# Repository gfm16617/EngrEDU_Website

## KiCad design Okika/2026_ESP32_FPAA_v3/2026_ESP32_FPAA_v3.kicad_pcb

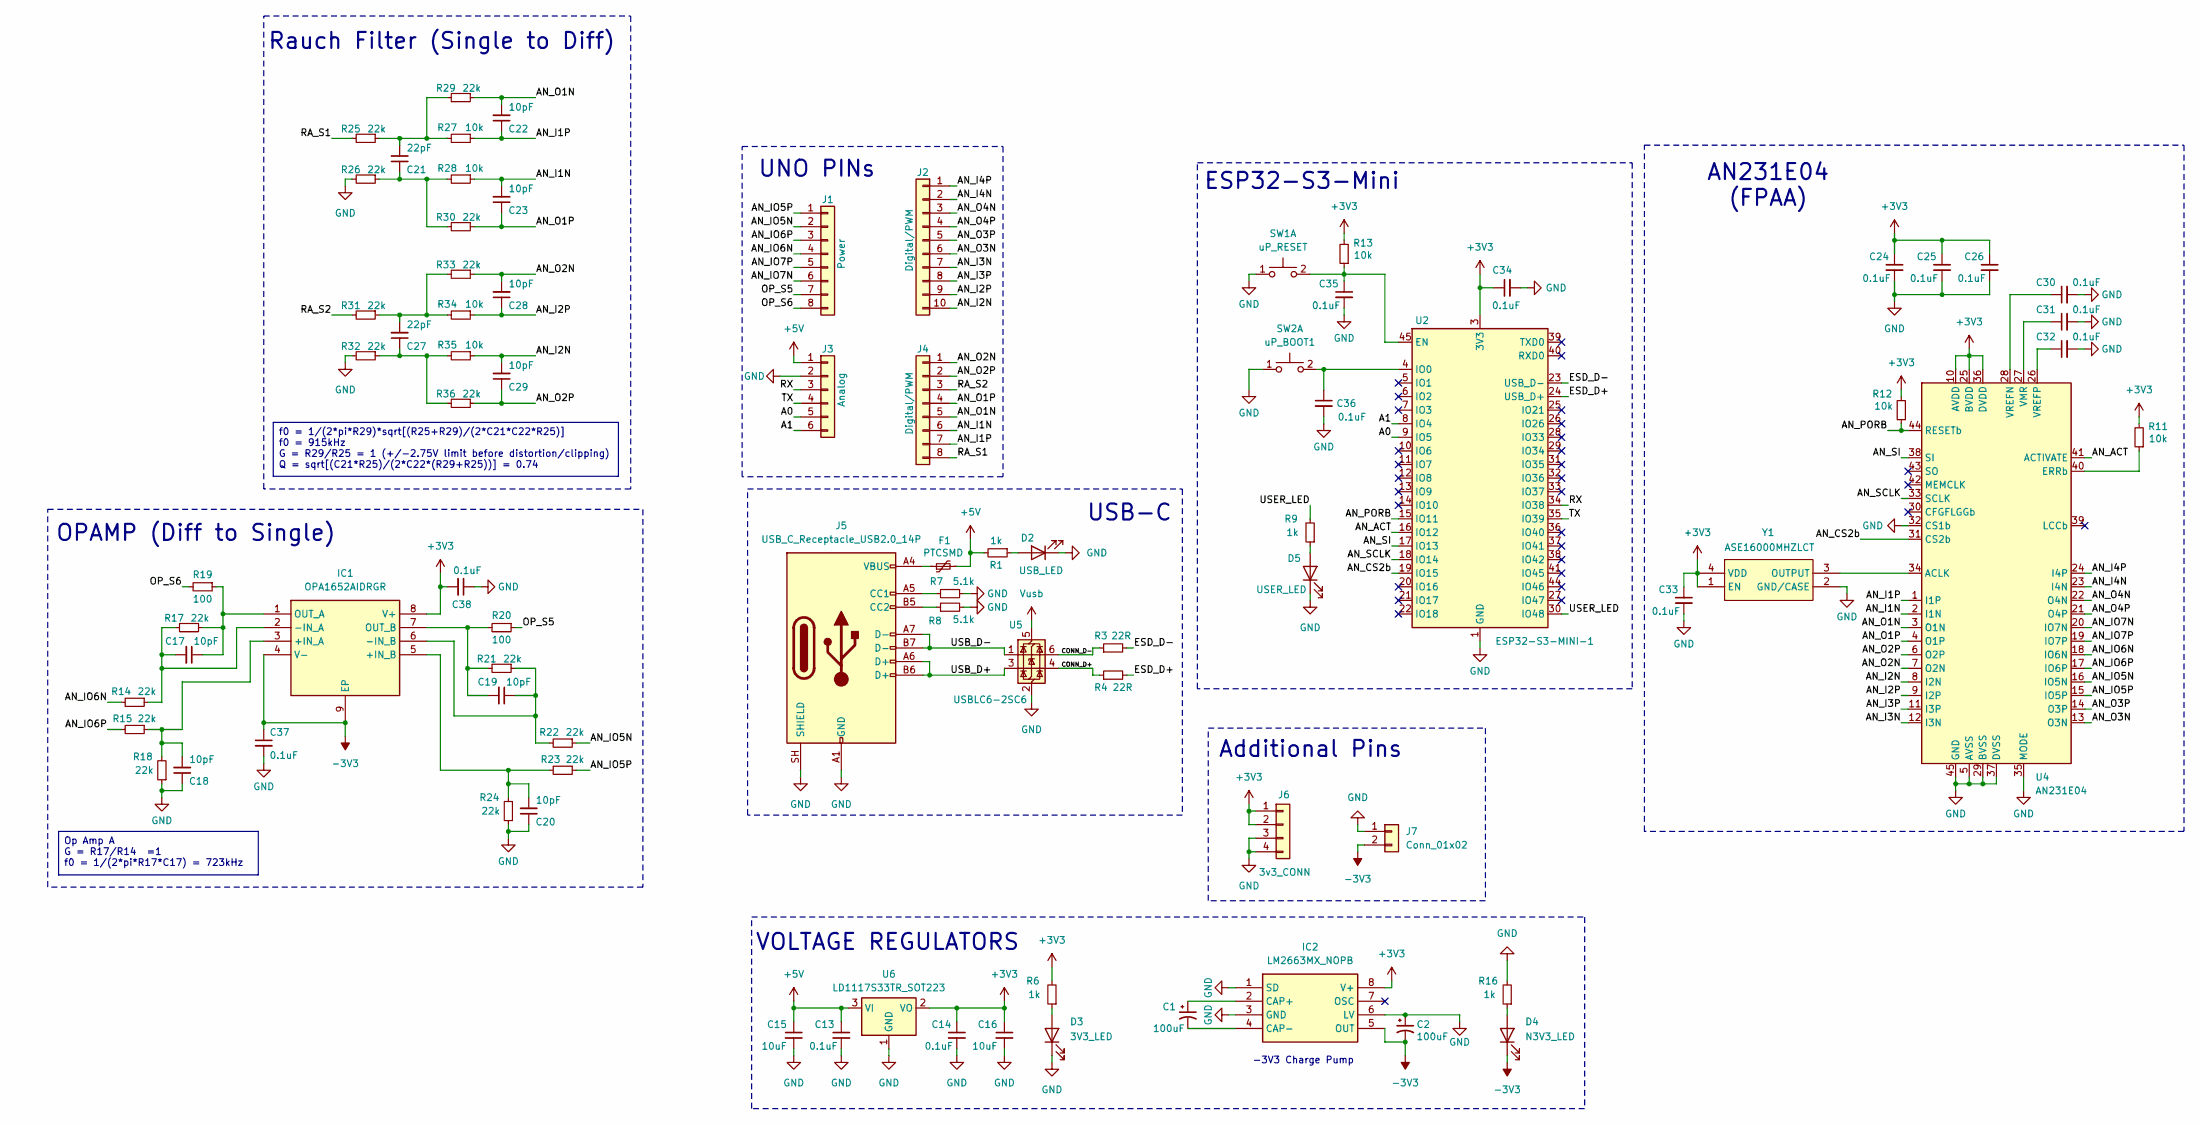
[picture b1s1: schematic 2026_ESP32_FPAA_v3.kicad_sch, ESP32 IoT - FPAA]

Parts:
C1, C2: 100uF; CAPPM7343X310N; Mfr # 593D107X9010D2TE3
C13, C14, C34, C35, C36, C37, C38: 0.1uF; C_0805_2012Metric_Pad1.18x1.45mm_HandSolder; Mfr # C0805C104K4JACAUTO
C15, C16: 10uF; C_0805_2012Metric_Pad1.18x1.45mm_HandSolder; Mfr # C0805C106K4PACTU
C17, C18, C19, C20, C22, C23, C28, C29: 10pF; C_0603_1608Metric_Pad1.08x0.95mm_HandSolder; Mfr # 08052U100JAT2A
C21, C27: 22pF; C_0603_1608Metric_Pad1.08x0.95mm_HandSolder; Mfr # C0603C220G3HACTU
C24, C25, C26, C30, C31, C32, C33: 0.1uF; C_0603_1608Metric_Pad1.08x0.95mm_HandSolder; Mfr # CC0603JRX7R9BB104
D2: USB_LED; LED_0805_2012Metric_Pad1.15x1.40mm_HandSolder; Mfr # 150080BS75000
D3: 3V3_LED; LED_0805_2012Metric_Pad1.15x1.40mm_HandSolder; Mfr # 150080BS75000
D4: N3V3_LED; LED_0805_2012Metric_Pad1.15x1.40mm_HandSolder; Mfr # 150080BS75000
D5: USER_LED; LED_0805_2012Metric_Pad1.15x1.40mm_HandSolder; Mfr # 150080BS75000
F1: PTCSMD; Fuse_1812_4532Metric; Mfr # MF-MSMF050-2
IC1: OPA1652AIDRGR; SON50P300X300X80-9N-D; Manufacturer_Part_Number OPA1652AIDRGR; Mouser Part Number 595-OPA1652AIDRGR
IC2: LM2663MX_NOPB; SOIC127P600X175-8N; Manufacturer_Part_Number LM2663MX/NOPB; Mouser Part Number 926-LM2663MX/NOPB
J1: Power; PinSocket_1x08_P2.54mm_Vertical
J2: Digital/PWM; PinSocket_1x10_P2.54mm_Vertical
J3: Analog; PinSocket_1x06_P2.54mm_Vertical
J4: Digital/PWM; PinSocket_1x08_P2.54mm_Vertical
J5: USB_C_Receptacle_USB2.0_14P; USB_C_Receptacle_HCTL_HC-TYPE-C-16P-01A; Mfg Part# UJ20-C-H-C-4-SMT-TR
J6: 3v3_CONN; PinHeader_1x04_P2.54mm_Vertical
J7: Conn_01x02; PinHeader_1x02_P2.54mm_Vertical
R1, R6, R9, R16: 1k; R_0805_2012Metric_Pad1.20x1.40mm_HandSolder; Mfr # TNPW08051K00FEEA
R3, R4: 22R; R_0805_2012Metric_Pad1.20x1.40mm_HandSolder; Mfr # RCA080522R0FKEA
R7: 5.1k; R_0805_2012Metric_Pad1.20x1.40mm_HandSolder; Mfg Part# AC0805FR-075K1L
R8: 5.1k; R_0805_2012Metric_Pad1.20x1.40mm_HandSolder; Mfg Part# CRCW06035K10FKEC
R11, R12, R27, R28, R34, R35: 10k; R_0603_1608Metric_Pad0.98x0.95mm_HandSolder; Mfr # AC0805DR-0710KL
R13: 10k; R_0805_2012Metric_Pad1.20x1.40mm_HandSolder; Mfr # AC0805DR-0710KL
R14, R15, R17, R18, R21, R22, R23, R24, R25, R26, R29, R30, R31, R32, R33, R36: 22k; R_0603_1608Metric_Pad0.98x0.95mm_HandSolder; Mfr # RT0805DRD0722KL
R19, R20: 100; R_0603_1608Metric_Pad0.98x0.95mm_HandSolder; Mfr # RT0805FRE10100RL
SW1: uP_RESET; SW_SWT7015-006010SSA_REVA; Mfr # SWT7015-006010SSA
SW2: uP_BOOT1; SW_SWT7015-006010SSA_REVA; Mfr # SWT7015-006010SSA
U2: ESP32-S3-MINI-1; ESP32-S2-MINI-1; Mfr # ESP32-S3-MINI-1-N8
U4: AN231E04; QFN-44-1EP_7x7mm_P0.5mm_EP5.15x5.15mm; Part # AN231E04
U5: USBLC6-2SC6; SOT-23-6; Mfr # USBLC6-2SC6
U6: LD1117S33TR_SOT223; SOT-223-3_TabPin2; Mfr # LD1117S33TR
Y1: ASE16000MHZLCT; ASE24576MHZLCT; Manufacturer_Part_Number ASE16000MHZLCT

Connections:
+3V3: C14.1, C16.1, C24.1, C25.1, C26.1, C33.1, C34.1, C38.2, IC1.8 (V+), IC2.8 (V+), J6.1, J6.2, R6.2, R11.2, R12.2, R13.2, U2.3 (3V3), U4.10 (AVDD), U4.25 (BVDD), U4.36 (DVDD), U6.2 (VO), Y1.1 (EN), Y1.4 (VDD)
+5V: C13.1, C15.1, F1.2, J3.1, R1.2, U6.3 (VI)
-3V3: C2.2, C37.1, D4.1 (K), IC1.4 (V-), IC1.9 (EP), IC2.5 (OUT), J7.2
/A0: J3.5, U2.9 (IO5)
/A1: J3.6, U2.8 (IO4)
/AN_ACT: U2.16 (IO12), U4.41 (ACTIVATE)
/AN_CS2b: U2.19 (IO15), U4.31 (CS2b)
/AN_I1N: C23.2, J4.6, R28.1, U4.2 (I1N)
/AN_I1P: C22.1, J4.7, R27.1, U4.1 (I1P)
/AN_I2N: C29.2, J2.10, R35.1, U4.8 (I2N)
/AN_I2P: C28.1, J2.9, R34.1, U4.9 (I2P)
/AN_I3N: J2.7, U4.12 (I3N)
/AN_I3P: J2.8, U4.11 (I3P)
/AN_I4N: J2.2, U4.23 (I4N)
/AN_I4P: J2.1, U4.24 (I4P)
/AN_IO5N: J1.2, R22.1, U4.16 (IO5N)
/AN_IO5P: J1.1, R23.1, U4.15 (IO5P)
/AN_IO6N: J1.4, R14.2, U4.18 (IO6N)
/AN_IO6P: J1.3, R15.2, U4.17 (IO6P)
/AN_IO7N: J1.6, U4.20 (IO7N)
/AN_IO7P: J1.5, U4.19 (IO7P)
/AN_O1N: C22.2, J4.5, R29.1, U4.3 (O1N)
/AN_O1P: C23.1, J4.4, R30.1, U4.4 (O1P)
/AN_O2N: C28.2, J4.1, R33.1, U4.7 (O2N)
/AN_O2P: C29.1, J4.2, R36.1, U4.6 (O2P)
/AN_O3N: J2.6, U4.13 (O3N)
/AN_O3P: J2.5, U4.14 (O3P)
/AN_O4N: J2.3, U4.22 (O4N)
/AN_O4P: J2.4, U4.21 (O4P)
/AN_PORB: R12.1, U2.15 (IO11), U4.44 (RESETb)
/AN_SCLK: U2.18 (IO14), U4.33 (SCLK)
/AN_SI: U2.17 (IO13), U4.38 (SI)
/CONN_D+: R4.1, U5.4 (I/O2)
/CONN_D-: R3.1, U5.6 (I/O1)
/ESD_D+: R4.2, U2.24 (USB_D+)
/ESD_D-: R3.2, U2.23 (USB_D-)
/OP_S5: J1.7, R20.1
/OP_S6: J1.8, R19.2
/RA_S1: J4.8, R25.2
/RA_S2: J4.3, R31.2
/RX: J3.3, U2.34 (IO38)
/TX: J3.4, U2.35 (IO39)
/USB_D+: J5.A6 (D+), J5.B6 (D+), U5.3 (I/O2)
/USB_D-: J5.A7 (D-), J5.B7 (D-), U5.1 (I/O1)
/USER_LED: R9.2, U2.30 (IO48)
GND: C2.1, C13.2, C14.2, C15.2, C16.2, C18.1, C20.1, C24.2, C25.2, C26.2, C30.2, C31.2, C32.2, C33.2, C34.2, C35.2, C36.2, C37.2, C38.1, D2.1 (K), D3.1 (K), D5.1 (K), IC2.1 (SD), IC2.3 (GND), IC2.6 (LV), J3.2, J5.A1 (GND), J5.A12 (GND), J5.B1 (GND), J5.B12 (GND), J5.SH (SHIELD), J6.3, J6.4, J7.1, R7.1, R8.2, R16.2, R18.1, R24.1, R26.2, R32.2, SW1.1 (C), SW2.1 (C), U2.1 (GND), U2.2 (GND), U2.42 (GND), U2.43 (GND), U2.46 (GND), U2.47 (GND), U2.48 (GND), U2.49 (GND), U2.50 (GND), U2.51 (GND), U2.52 (GND), U2.53 (GND), U2.54 (GND), U2.55 (GND), U2.56 (GND), U2.57 (GND), U2.58 (GND), U2.59 (GND), U2.60 (GND), U2.61 (GND), U2.62 (GND), U2.63 (GND), U2.64 (GND), U2.65 (GND), U4.5 (AVSS), U4.29 (BVSS), U4.32 (CS1b), U4.35 (MODE), U4.37 (DVSS), U4.45 (GND), U5.2 (GND), U6.1 (GND), Y1.2 (GND/CASE)
unnamed: C21.1, R26.1, R28.2, R30.2
unnamed: C21.2, R25.1, R27.2, R29.2
unnamed: C27.1, R32.1, R35.2, R36.2
unnamed: C27.2, R31.1, R33.2, R34.2
unnamed: D2.2 (A), R1.1
unnamed: D3.2 (A), R6.1
unnamed: D4.2 (A), R16.1
unnamed: D5.2 (A), R9.1
unnamed: F1.1, J5.A4 (VBUS), J5.A9 (VBUS), J5.B4 (VBUS), J5.B9 (VBUS)
unnamed: C18.2, IC1.3 (+IN_A), R15.1, R18.2
unnamed: C20.2, IC1.5 (+IN_B), R23.2, R24.2
unnamed: C17.2, IC1.2 (-IN_A), R14.1, R17.2
unnamed: C19.1, IC1.6 (-IN_B), R21.1, R22.2
unnamed: C17.1, IC1.1 (OUT_A), R17.1, R19.1
unnamed: C19.2, IC1.7 (OUT_B), R20.2, R21.2
unnamed: C1.1, IC2.2 (CAP+)
unnamed: C1.2, IC2.4 (CAP-)
unnamed: J5.A5 (CC1), R7.2
unnamed: J5.B5 (CC2), R8.1
unnamed: C35.1, R13.1, SW1.2 (D), U2.45 (EN)
unnamed: C36.1, SW2.2 (D), U2.4 (IO0)
unnamed: U4.34 (ACLK), Y1.3 (OUTPUT)
unnamed: R11.1, U4.40 (ERRb)
unnamed: C31.1, U4.27 (VMR)
unnamed: C30.1, U4.28 (VREFN)
unnamed: C32.1, U4.26 (VREFP)
Vusb: U5.5 (VBUS)

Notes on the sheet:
USB-C
ESP32-S3-Mini
Additional Pins
OPAMP (Diff to Single)
-3V3 Charge Pump
VOLTAGE REGULATORS
Rauch Filter (Single to Diff)
AN231E04 (FPAA)
UNO PINs
f0 = 1/(2*pi*R29)*sqrt[(R25+R29)/(2*C21*C22*R25)] f0 = 915kHz G = R29/R25 = 1 (+/-2.75V limit before distortion/clipping) Q = sqrt[(C21*R25)/(2*C22*(R29+R25))] = 0.74
Op Amp A G = R17/R14 =1 f0 = 1/(2*pi*R17*C17) = 723kHz

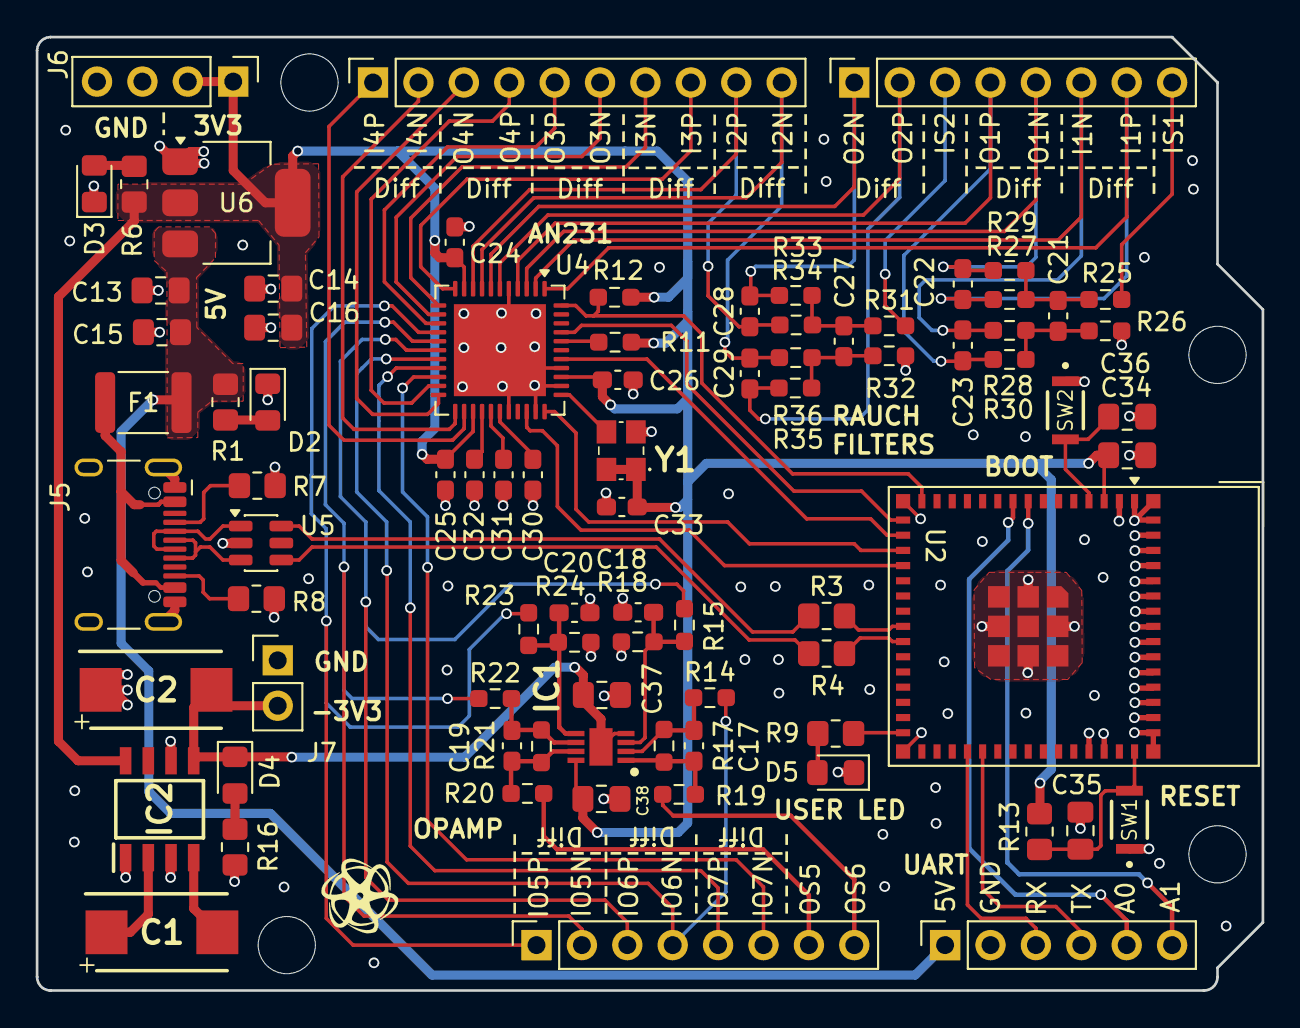
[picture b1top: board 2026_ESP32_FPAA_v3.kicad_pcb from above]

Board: 4 copper layers, 68.6 x 53.3 mm, 86 parts (0 on the bottom side), 72 nets.

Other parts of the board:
MH1, MH2, MH3, MH4: MountingHole_3.2mm

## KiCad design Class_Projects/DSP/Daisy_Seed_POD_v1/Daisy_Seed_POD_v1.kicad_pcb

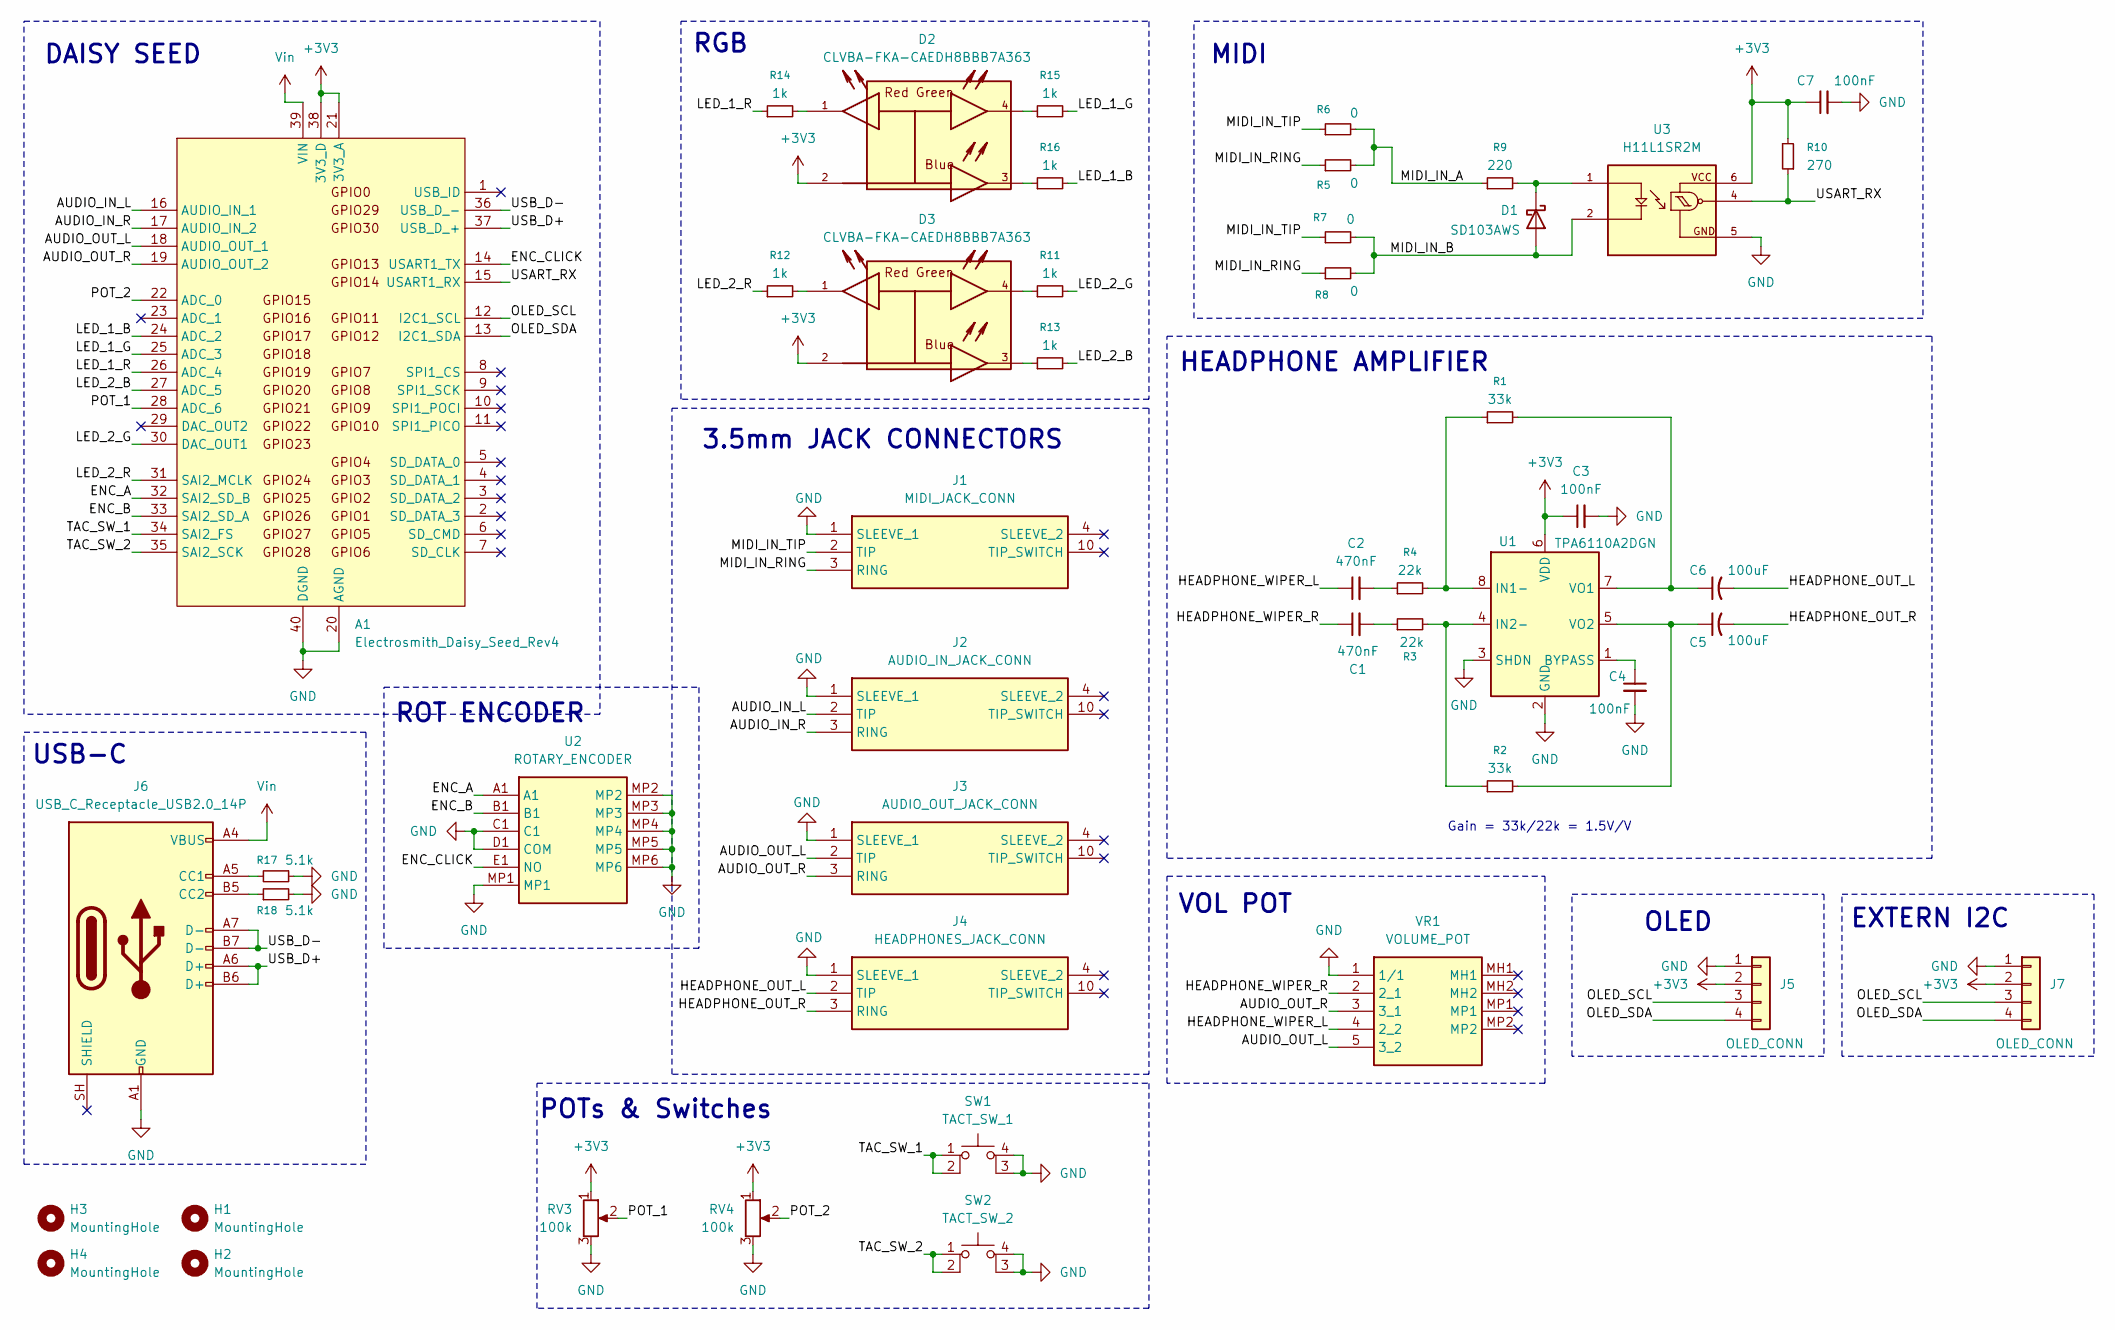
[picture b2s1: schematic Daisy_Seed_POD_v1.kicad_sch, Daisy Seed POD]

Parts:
A1: Electrosmith_Daisy_Seed_Rev4; Electrosmith_Daisy_Seed
C1, C2: 470nF; C_0805_2012Metric; Mfr # GCJ21BL8EH474KA07L
C3, C4, C7: 100nF; C_0805_2012Metric; Mfr # 0805YC104M4T2A
C5, C6: 100uF; CAP_EEE1AA101SP; Mfr # EEE-1AA101SP
D1: SD103AWS; SOD2513X120N; Mfr # SD103AWS-7-F
D2, D3: CLVBA-FKA-CAEDH8BBB7A363; SOL150P350X210-4N; PARTREV N/A
H1, H2, H3, H4: MountingHole; MountingHole_3.2mm_M3_Pad_Via
J1: MIDI_JACK_CONN; SJ235863B1SMTTR; Manufacturer_Part_Number SJ2-35863B1-SMT-TR; Mouser Part Number 490-SJ2-35863B1SMTTR
J2: AUDIO_IN_JACK_CONN; SJ235863B1SMTTR; Manufacturer_Part_Number SJ2-35863B1-SMT-TR; Mouser Part Number 490-SJ2-35863B1SMTTR
J3: AUDIO_OUT_JACK_CONN; SJ235863B1SMTTR; Manufacturer_Part_Number SJ2-35863B1-SMT-TR; Mouser Part Number 490-SJ2-35863B1SMTTR
J4: HEADPHONES_JACK_CONN; SJ235863B1SMTTR; Manufacturer_Part_Number SJ2-35863B1-SMT-TR; Mouser Part Number 490-SJ2-35863B1SMTTR
J5, J7: OLED_CONN; PinSocket_1x04_P2.54mm_Vertical
J6: USB_C_Receptacle_USB2.0_14P; USB_C_Receptacle_HCTL_HC-TYPE-C-16P-01A; Mfg Part# UJ20-C-H-C-4-SMT-TR
R1, R2: 33k; R_0805_2012Metric; Mfr # AF0805JR-0733KL
R3, R4: 22k; R_0805_2012Metric; Mfr # ERJ-U06F2202V
R5, R6, R7, R8: 0; R_0805_2012Metric; Mfr # CR0805AJ/-000EAS
R9: 220; R_0805_2012Metric; Mfr # CRGH0805F220R
R10: 270; R_0805_2012Metric; Mfr # AA0805FR-07220RL
R11, R12, R13, R14, R15, R16: 1k; R_0805_2012Metric; Mfr # CRCW08051K00FKEA
R17, R18: 5.1k; R_0805_2012Metric; Mfr # MCU08050C5101FP500
RV3, RV4: 100k; Potentiometer_Bourns_3386P_Vertical
SW1: TACT_SW_1; SW_SKRPACE010; Mfr # SKRPACE010
SW2: TACT_SW_2; SW_SKRPACE010; Mfr # SKRPACE010
U1: TPA6110A2DGN; HVSSOP-8-1EP_3x3mm_P0.65mm_EP1.57x1.89mm; Mfr # TPA6110A2DGNR
U2: ROTARY_ENCODER; PEC11J9220FH0015; Manufacturer_Part_Number PEC11J-9220F-H0015; Mouser Part Number 652-PEC11J9220FH0015
U3: H11L1SR2M; PARTREV 3
VR1: VOLUME_POT; RK10J12R0A0B; Manufacturer_Part_Number RK10J12R0A0B; Mouser Part Number 688-RK10J12R0A0B

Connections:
+3V3: A1.21 (3V3_A), A1.38 (3V3_D), C3.1, C7.1, D2.2, D3.2, J5.2, J7.2, R10.2, RV3.1, RV4.1, U1.6 (VDD), U3.6
/AUDIO_IN_L: A1.16 (AUDIO_IN_1), J2.2 (TIP)
/AUDIO_IN_R: A1.17 (AUDIO_IN_2), J2.3 (RING)
/AUDIO_OUT_L: A1.18 (AUDIO_OUT_1), J3.2 (TIP), VR1.5 (3_2)
/AUDIO_OUT_R: A1.19 (AUDIO_OUT_2), J3.3 (RING), VR1.3 (3_1)
/ENC_A: A1.32 (SAI2_SD_B), U2.A1
/ENC_B: A1.33 (SAI2_SD_A), U2.B1
/ENC_CLICK: A1.14 (USART1_TX), U2.E1 (NO)
/HEADPHONE_OUT_L: C6.2, J4.2 (TIP)
/HEADPHONE_OUT_R: C5.2, J4.3 (RING)
/HEADPHONE_WIPER_L: C2.1, VR1.4 (2_2)
/HEADPHONE_WIPER_R: C1.1, VR1.2 (2_1)
/LED_1_B: A1.24 (ADC_2), R16.2
/LED_1_G: A1.25 (ADC_3), R15.2
/LED_1_R: A1.26 (ADC_4), R14.1
/LED_2_B: A1.27 (ADC_5), R13.2
/LED_2_G: A1.30 (DAC_OUT1), R11.2
/LED_2_R: A1.31 (SAI2_MCLK), R12.1
/MIDI_IN_A: R5.2, R6.2, R9.1
/MIDI_IN_B: D1.2 (A), R7.2, R8.2, U3.2
/MIDI_IN_RING: J1.3 (RING), R5.1, R8.1
/MIDI_IN_TIP: J1.2 (TIP), R6.1, R7.1
/OLED_SCL: A1.12 (I2C1_SCL), J5.3, J7.3
/OLED_SDA: A1.13 (I2C1_SDA), J5.4, J7.4
/POT_1: A1.28 (ADC_6), RV3.2
/POT_2: A1.22 (ADC_0), RV4.2
/TAC_SW_1: A1.34 (SAI2_FS), SW1.1, SW1.2
/TAC_SW_2: A1.35 (SAI2_SCK), SW2.1, SW2.2
/USART_RX: A1.15 (USART1_RX), R10.1, U3.4
/USB_D+: A1.37 (USB_D_+), J6.A6 (D+), J6.B6 (D+)
/USB_D-: A1.36 (USB_D_-), J6.A7 (D-), J6.B7 (D-)
GND: A1.20 (AGND), A1.40 (DGND), C3.2, C4.2, C7.2, J1.1 (SLEEVE_1), J2.1 (SLEEVE_1), J3.1 (SLEEVE_1), J4.1 (SLEEVE_1), J5.1, J6.A1 (GND), J6.A12 (GND), J6.B1 (GND), J6.B12 (GND), J7.1, R17.1, R18.2, RV3.3, RV4.3, SW1.3 (K), SW1.4 (A), SW2.3 (K), SW2.4 (A), U1.2 (GND), U1.3 (SHDN), U1.9 (GND), U2.C1, U2.D1 (COM), U2.MP1, U2.MP2, U2.MP3, U2.MP4, U2.MP5, U2.MP6, U3.5, VR1.1 (1/1)
unnamed: C1.2, R3.1
unnamed: C2.2, R4.1
unnamed: D1.1 (K), R9.2, U3.1
unnamed: D2.1, R14.2
unnamed: D2.3, R16.1
unnamed: D2.4, R15.1
unnamed: D3.1, R12.2
unnamed: D3.3, R13.1
unnamed: D3.4, R11.1
unnamed: J6.A5 (CC1), R17.2
unnamed: J6.B5 (CC2), R18.1
unnamed: C4.1, U1.1 (BYPASS)
unnamed: R1.1, R4.2, U1.8 (IN1-)
unnamed: R2.1, R3.2, U1.4 (IN2-)
unnamed: C6.1, R1.2, U1.7 (VO1)
unnamed: C5.1, R2.2, U1.5 (VO2)
Vin: A1.39 (VIN), J6.A4 (VBUS), J6.A9 (VBUS), J6.B4 (VBUS), J6.B9 (VBUS)

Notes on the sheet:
EXTERN I2C
HEADPHONE AMPLIFIER
ROT ENCODER
MIDI
RGB
VOL POT
OLED
USB-C
POTs & Switches
DAISY SEED
Gain = 33k/22k = 1.5V/V
3.5mm JACK CONNECTORS

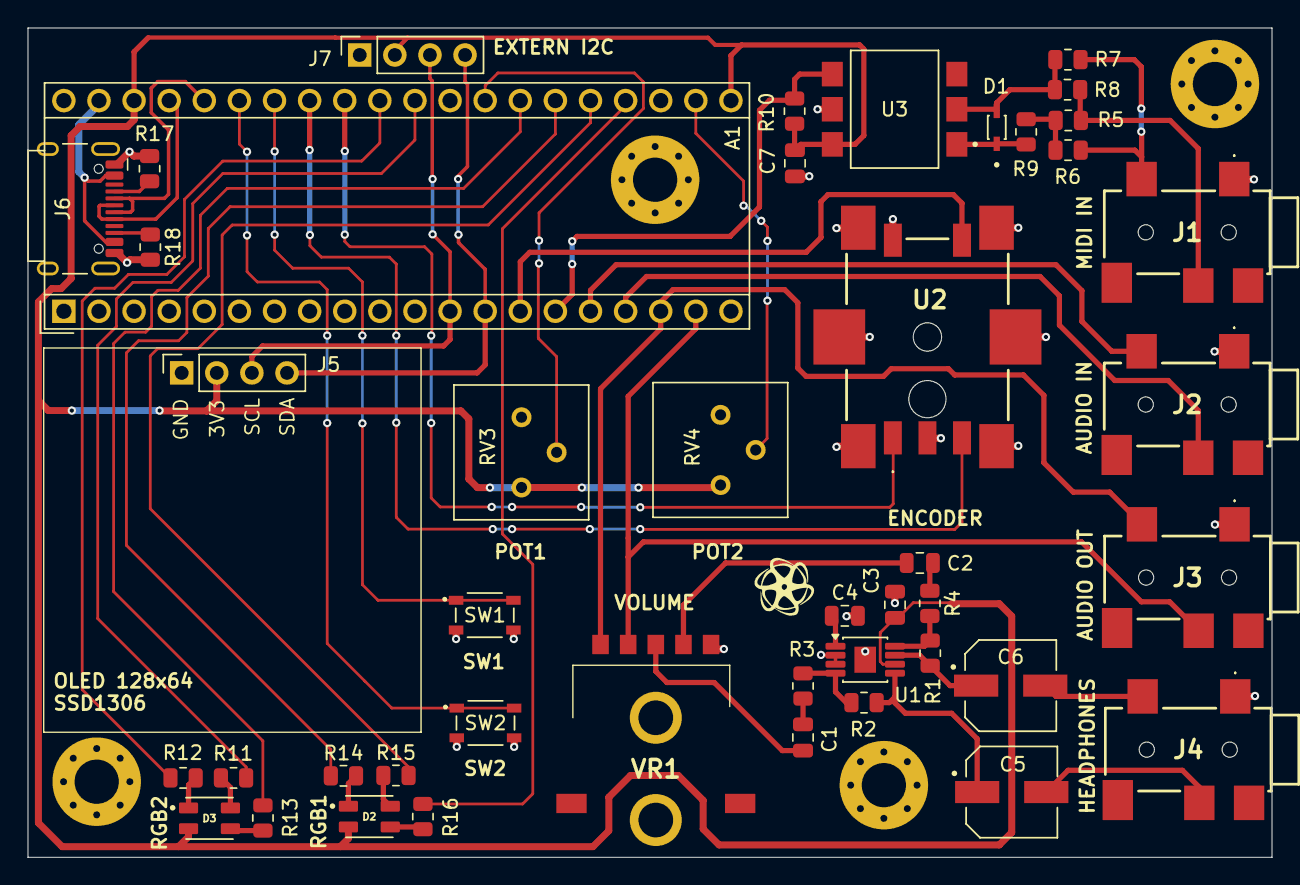
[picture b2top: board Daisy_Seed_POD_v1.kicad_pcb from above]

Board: 2 copper layers, 90.0 x 60.0 mm, 48 parts (0 on the bottom side), 49 nets.

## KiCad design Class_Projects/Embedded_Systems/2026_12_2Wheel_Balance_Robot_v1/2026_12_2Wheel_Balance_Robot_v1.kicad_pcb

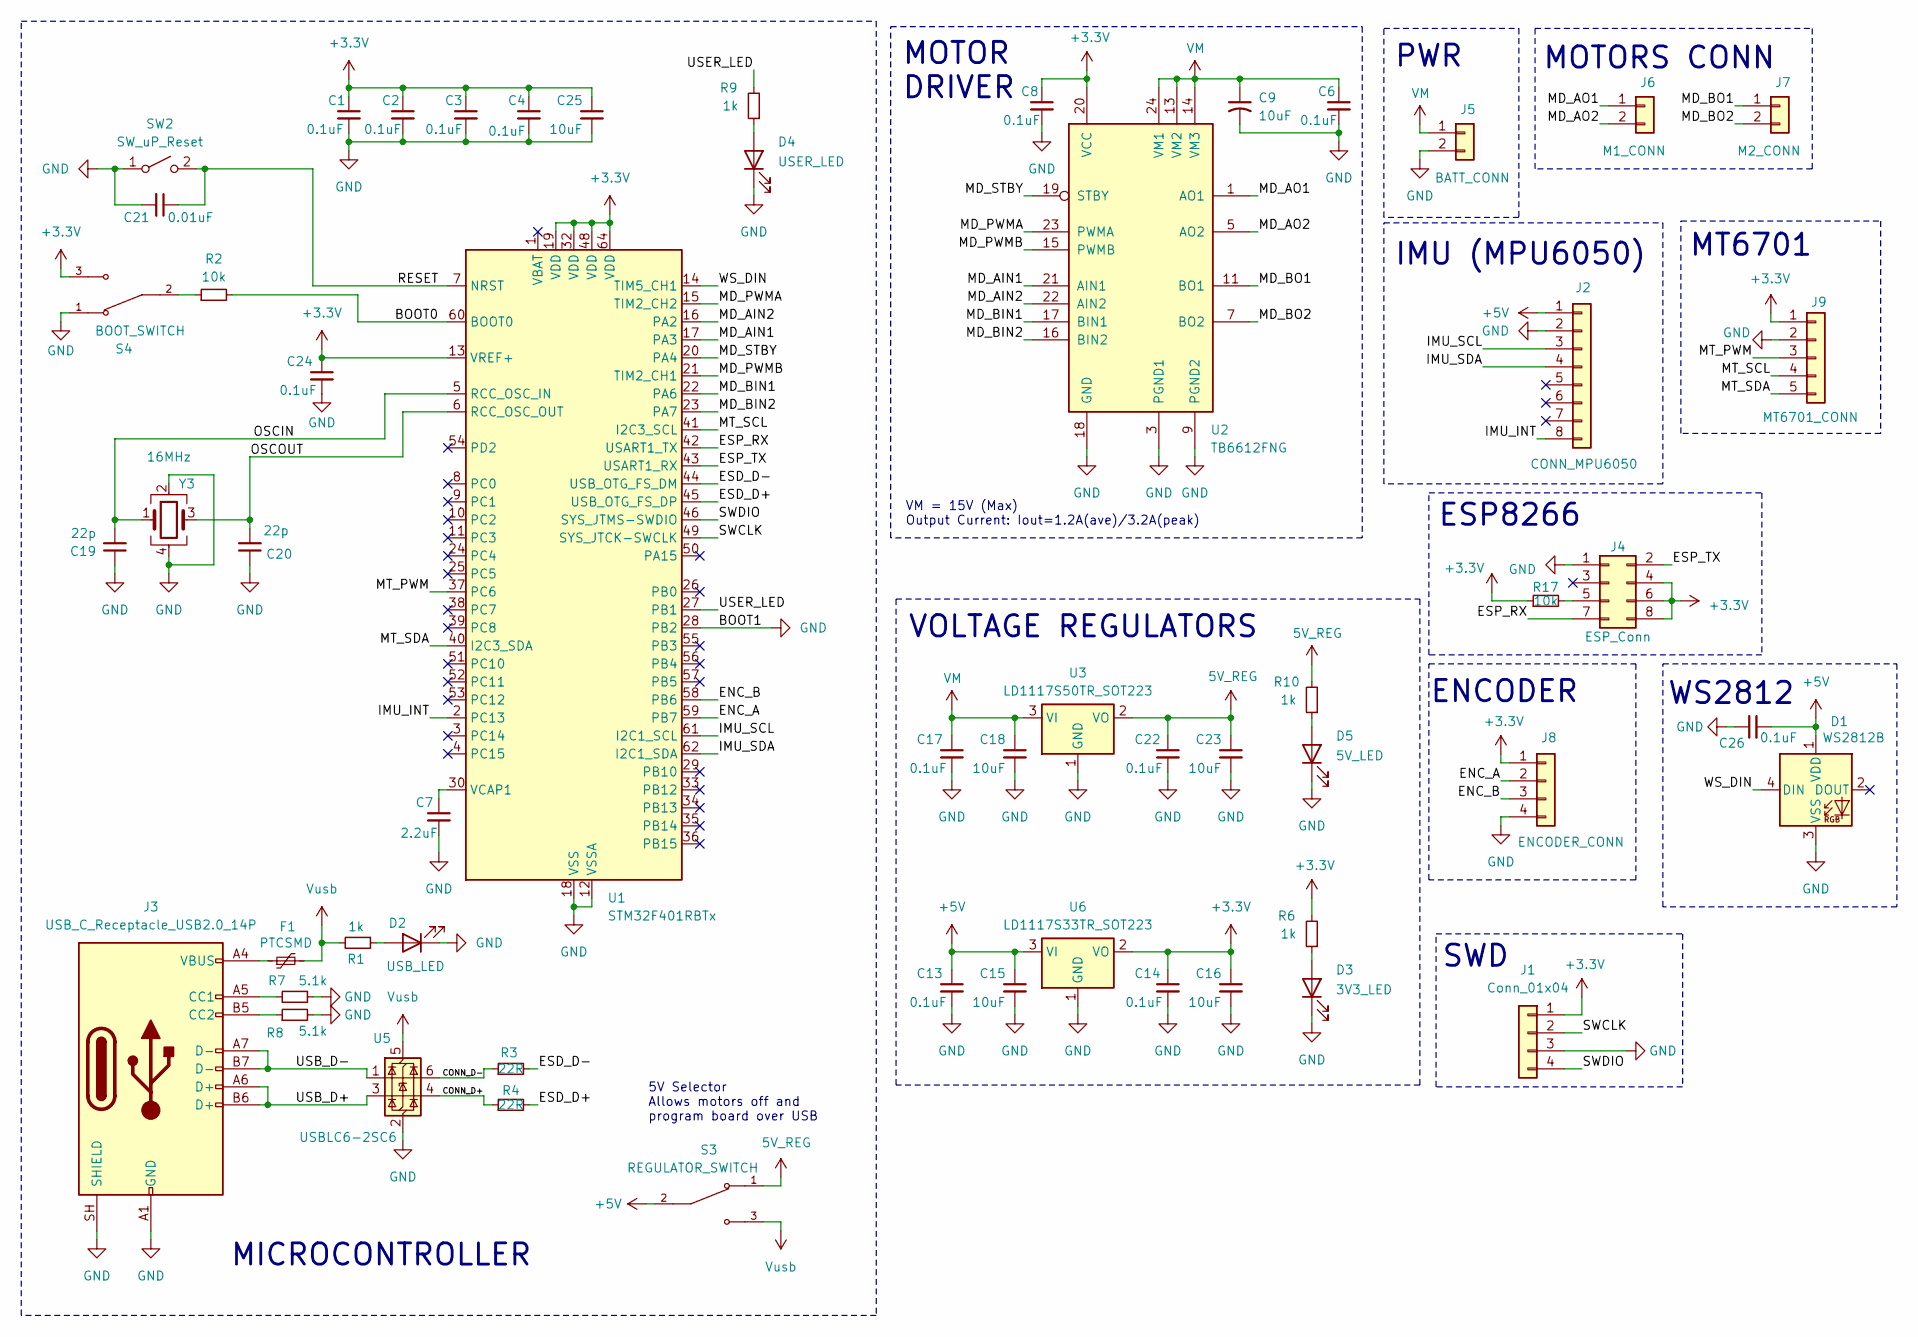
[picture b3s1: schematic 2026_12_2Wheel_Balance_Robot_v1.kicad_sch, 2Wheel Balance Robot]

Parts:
C1, C2, C3, C4, C6, C8, C13, C14, C17, C22, C24, C26: 0.1uF; C_0805_2012Metric_Pad1.18x1.45mm_HandSolder; Mfr # C0805C104K4JACAUTO
C7: 2.2uF; C_0805_2012Metric_Pad1.18x1.45mm_HandSolder; Mfr # C0805X225K3RACAUTO
C9: 10uF; CP_EIA-6032-28_Kemet-C_HandSolder; Mfr # TPSC106M025R0500
C15, C16, C18, C23: 10uF; C_0805_2012Metric_Pad1.18x1.45mm_HandSolder; Mfr # C0805C106K4PACTU
C19, C20: 22p; C_0805_2012Metric_Pad1.18x1.45mm_HandSolder; Mfg Part# 08055C220KAT2A
C21: 0.01uF; C_0805_2012Metric_Pad1.18x1.45mm_HandSolder; Mfg Part# KAF21BR72A103JT
C25: 10uF; C_0805_2012Metric_Pad1.18x1.45mm_HandSolder; Mfg Part# C0805C106K4PACTU
D1: WS2812B; LED_WS2812B_PLCC4_5.0x5.0mm_P3.2mm; Mfr # FZ2812-5050; Mouser Digikey Part
D2: USB_LED; LED_0805_2012Metric_Pad1.15x1.40mm_HandSolder; Mfr # 150080BS75000
D3: 3V3_LED; LED_0805_2012Metric_Pad1.15x1.40mm_HandSolder; Mfr # 150080BS75000
D4: USER_LED; LED_0805_2012Metric_Pad1.15x1.40mm_HandSolder; Mfr # 150080BS75000
D5: 5V_LED; LED_0805_2012Metric_Pad1.15x1.40mm_HandSolder; Mfr # 150080BS75000
F1: PTCSMD; Fuse_1812_4532Metric; Mfr # MF-MSMF050-2
J1: Conn_01x04; PinHeader_1x04_P2.54mm_Vertical
J2: CONN_MPU6050; PinSocket_1x08_P2.54mm_Vertical
J3: USB_C_Receptacle_USB2.0_14P; USB_C_Receptacle_HCTL_HC-TYPE-C-16P-01A; Mfg Part# UJ20-C-H-C-4-SMT-TR
J4: ESP_Conn; PinSocket_2x04_P2.54mm_Vertical
J5: BATT_CONN; JST_XH_B2B-XH-A_1x02_P2.50mm_Vertical
J6: M1_CONN; JST_XH_B2B-XH-A_1x02_P2.50mm_Vertical
J7: M2_CONN; JST_XH_B2B-XH-A_1x02_P2.50mm_Vertical
J8: ENCODER_CONN; JST_XH_B4B-XH-A_1x04_P2.50mm_Vertical
J9: MT6701_CONN; JST_XH_B5B-XH-A_1x05_P2.50mm_Vertical
R1, R6, R9, R10: 1k; R_0805_2012Metric_Pad1.20x1.40mm_HandSolder; Mfr # TNPW08051K00FEEA
R2, R17: 10k; R_0805_2012Metric_Pad1.20x1.40mm_HandSolder; Mfr # CPF0805B10KE1
R3, R4: 22R; R_0805_2012Metric_Pad1.20x1.40mm_HandSolder; Mfr # RCA080522R0FKEA
R7, R8: 5.1k; R_0603_1608Metric_Pad0.98x0.95mm_HandSolder; Mfg Part# CRCW06035K10FKEC
S3: REGULATOR_SWITCH; SW_SLW-66527511-SMT-TR; PARTREV 1.01
S4: BOOT_SWITCH; SW_SLW-66527511-SMT-TR; PARTREV 1.01
SW2: SW_uP_Reset; Mfg Part# 434121025816
U1: STM32F401RBTx; LQFP-64_10x10mm_P0.5mm; Mfr # STM32F401RBT6
U2: TB6612FNG; SSOP-24_5.3x8.2mm_P0.65mm; Mfr # TB6612FNG,C,8,EL
U3: LD1117S50TR_SOT223; SOT-223-3_TabPin2; Mfr # LD1117S50TR
U5: USBLC6-2SC6; SOT-23-6; Mfr # USBLC6-2SC6
U6: LD1117S33TR_SOT223; SOT-223-3_TabPin2; Mfr # LD1117S33TR
Y3: 16MHz; Crystal_SMD_Abracon_ABM8G-4Pin_3.2x2.5mm; Mfg Part# ABM8-16.000MHZ-D1X-T

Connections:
5V_REG: C22.1, C23.1, R10.2, S3.1, U3.2 (VO)
+3.3V: C1.1, C2.1, C3.1, C4.1, C8.1, C14.1, C16.1, C24.1, C25.1, J1.1, J4.4, J4.6, J4.8, J8.1, J9.1, R6.2, R17.1, S4.3, U1.13 (VREF+), U1.19 (VDD), U1.32 (VDD), U1.48 (VDD), U1.64 (VDD), U2.20 (VCC), U6.2 (VO)
+5V: C13.1, C15.1, C26.2, D1.1 (VDD), J2.1, S3.2, U6.3 (VI)
/BOOT0: R2.2, U1.60 (BOOT0)
/CONN_D+: R4.1, U5.4 (I/O2)
/CONN_D-: R3.1, U5.6 (I/O1)
/ENC_A: J8.2, U1.59 (PB7)
/ENC_B: J8.3, U1.58 (PB6)
/ESD_D+: R4.2, U1.45 (USB_OTG_FS_DP)
/ESD_D-: R3.2, U1.44 (USB_OTG_FS_DM)
/ESP_RX: J4.7, U1.42 (USART1_TX)
/ESP_TX: J4.2, U1.43 (USART1_RX)
/IMU_INT: J2.8, U1.2 (PC13)
/IMU_SCL: J2.3, U1.61 (I2C1_SCL)
/IMU_SDA: J2.4, U1.62 (I2C1_SDA)
/MD_AIN1: U1.17 (PA3), U2.21 (AIN1)
/MD_AIN2: U1.16 (PA2), U2.22 (AIN2)
/MD_AO1: J6.1, U2.1 (AO1), U2.2 (AO1)
/MD_AO2: J6.2, U2.5 (AO2), U2.6 (AO2)
/MD_BIN1: U1.22 (PA6), U2.17 (BIN1)
/MD_BIN2: U1.23 (PA7), U2.16 (BIN2)
/MD_BO1: J7.1, U2.11 (BO1), U2.12 (BO1)
/MD_BO2: J7.2, U2.7 (BO2), U2.8 (BO2)
/MD_PWMA: U1.15 (TIM2_CH2), U2.23 (PWMA)
/MD_PWMB: U1.21 (TIM2_CH1), U2.15 (PWMB)
/MD_STBY: U1.20 (PA4), U2.19 (STBY)
/MT_PWM: J9.3, U1.37 (PC6)
/MT_SCL: J9.4, U1.41 (I2C3_SCL)
/MT_SDA: J9.5, U1.40 (I2C3_SDA)
/OSCIN: C19.2, U1.5 (RCC_OSC_IN), Y3.1
/OSCOUT: C20.2, U1.6 (RCC_OSC_OUT), Y3.3
/RESET: C21.1, SW2.2 (B), U1.7 (NRST)
/SWCLK: J1.2, U1.49 (SYS_JTCK-SWCLK)
/SWDIO: J1.4, U1.46 (SYS_JTMS-SWDIO)
/USB_D+: J3.A6 (D+), J3.B6 (D+), U5.3 (I/O2)
/USB_D-: J3.A7 (D-), J3.B7 (D-), U5.1 (I/O1)
/USER_LED: R9.2, U1.27 (PB1)
/WS_DIN: D1.4 (DIN), U1.14 (TIM5_CH1)
GND: C1.2, C2.2, C3.2, C4.2, C6.2, C7.2, C8.2, C9.2, C13.2, C14.2, C15.2, C16.2, C17.2, C18.2, C19.1, C20.1, C21.2, C22.2, C23.2, C24.2, C25.2, C26.1, D1.3 (VSS), D2.1 (K), D3.1 (K), D4.1 (K), D5.1 (K), J1.3, J2.2, J3.A1 (GND), J3.A12 (GND), J3.B1 (GND), J3.B12 (GND), J3.SH (SHIELD), J4.1, J5.2, J8.4, J9.2, R7.1, R8.2, S4.1, SW2.1 (A), U1.12 (VSSA), U1.18 (VSS), U1.28 (PB2), U1.31 (VSS), U1.47 (VSS), U1.63 (VSS), U2.3 (PGND1), U2.4 (PGND1), U2.9 (PGND2), U2.10 (PGND2), U2.18 (GND), U3.1 (GND), U5.2 (GND), U6.1 (GND), Y3.2, Y3.4
unnamed: D2.2 (A), R1.1
unnamed: D3.2 (A), R6.1
unnamed: D4.2 (A), R9.1
unnamed: D5.2 (A), R10.1
unnamed: F1.1, J3.A4 (VBUS), J3.A9 (VBUS), J3.B4 (VBUS), J3.B9 (VBUS)
unnamed: J3.A5 (CC1), R7.2
unnamed: J3.B5 (CC2), R8.1
unnamed: J4.5, R17.2
unnamed: R2.1, S4.2
unnamed: C7.1, U1.30 (VCAP1)
VM: C6.1, C9.1, C17.1, C18.1, J5.1, U2.13 (VM2), U2.14 (VM3), U2.24 (VM1), U3.3 (VI)
Vusb: F1.2, R1.2, S3.3, U5.5 (VBUS)

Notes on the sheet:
5V Selector Allows motors off and program board over USB
MT6701
SWD
MOTORS CONN
IMU (MPU6050)
MOTOR DRIVER
VOLTAGE REGULATORS
ENCODER
MICROCONTROLLER
PWR
ESP8266
VM = 15V (Max) Output Current: Iout=1.2A(ave)/3.2A(peak)
WS2812

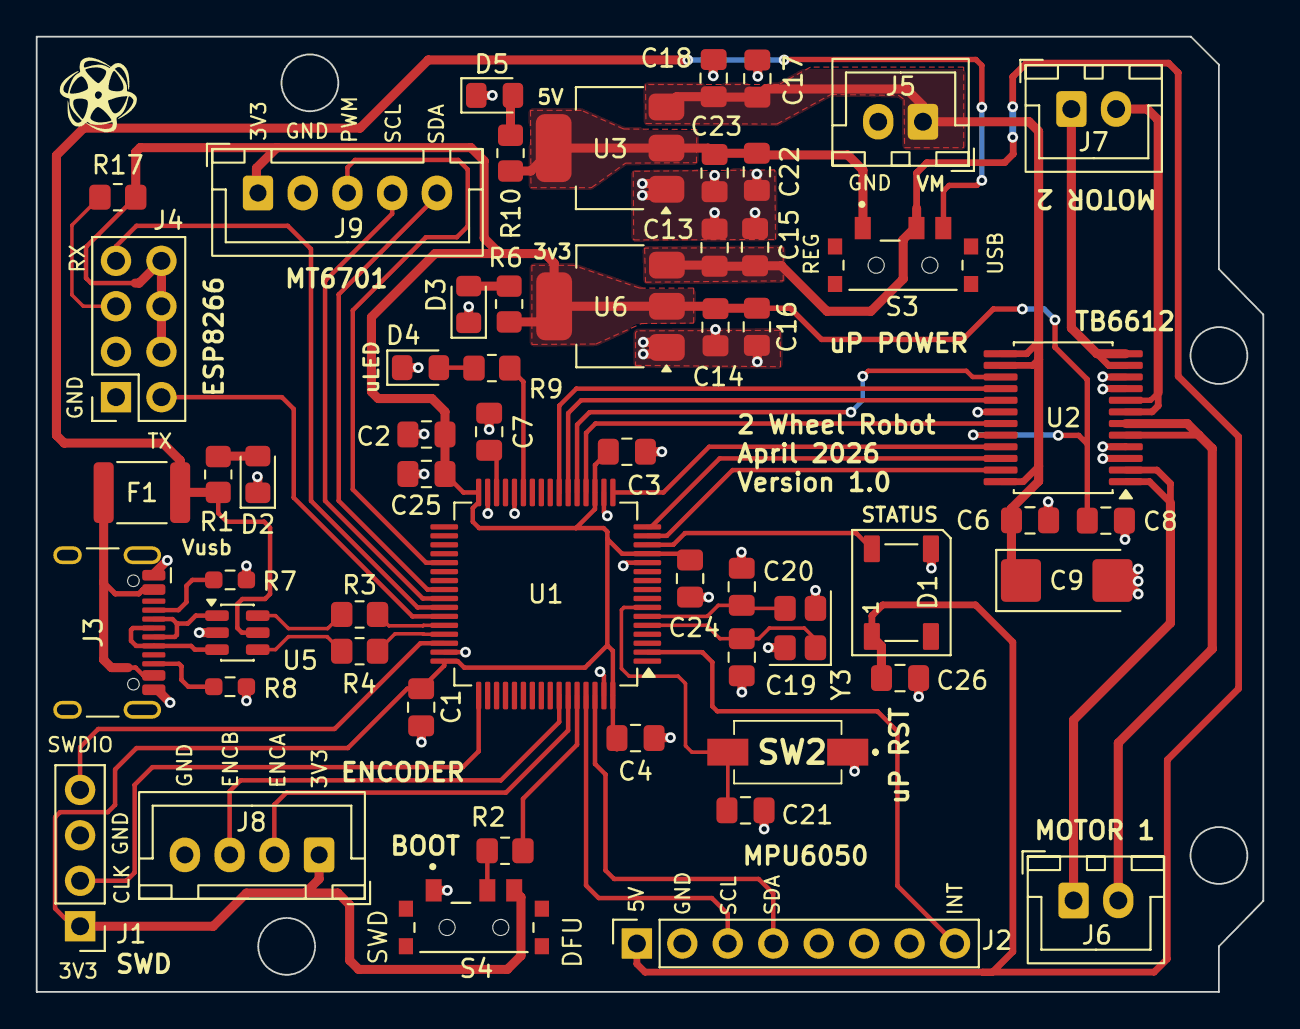
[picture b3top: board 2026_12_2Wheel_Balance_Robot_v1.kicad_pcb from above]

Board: 2 copper layers, 68.6 x 53.4 mm, 56 parts (0 on the bottom side), 51 nets.
